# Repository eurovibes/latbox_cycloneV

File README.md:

<!-- SPDX-FileCopyrightText: 2022 Benedikt Spranger <b.spranger@linutronix.de> -->
<!-- SPDX-License-Identifier: CERN-OHL-S-2.0 -->

# latbox_cycloneV - Cyclone V based latencybox

## License rules

latbox_cycloneV is provided under the terms of the CERN-OHL-S license
version 2 as provided in the LICENSES/CERN-OHL-S-2.0 file.

Instead of adding license boilerplates to the individual files,
latbox_cycloneV uses SPDX license identifiers, which are machine parseable
and considered legaly equivalent.

The SPDX license identifier in latbox_cycloneV shall be added at the first
possible line in a file which can contain a comment. This is normally the
first line except for scripts. Scripts require the #!PATH_TO_INTERPRETER tag
in the first line; place the SPDX identifier into the second line.

The SPDX license identifier is added in form of a comment.

## Copyright and License

Copyright Benedikt Spranger 2022.
This source describes Open Hardware and is licensed under the CERNOHL-S v2.
You may redistribute and modify this source and make products using it
under the terms of the CERN-OHL-S v2
(https://ohwr.org/cern ohl s v2.txt ).
This source is distributed WITHOUT ANY EXPRESS OR IMPLIED
WARRANTY, INCLUDING OF MERCHANTABILITY, SATISFACTORY
QUALITY AND FITNESS FOR A PARTICULAR PURPOSE. Please see
the CERN-OHL-S v2 for applicable conditions.
Source location: https://github.com/eurovibes/latbox_cycloneV
As per CERN-OHL-S v2 section 4, should You produce hardware based
on this source, You must where practicable maintain the Source Location
visible on the external case of the latbox_cycloneV or other products you
make using this source.

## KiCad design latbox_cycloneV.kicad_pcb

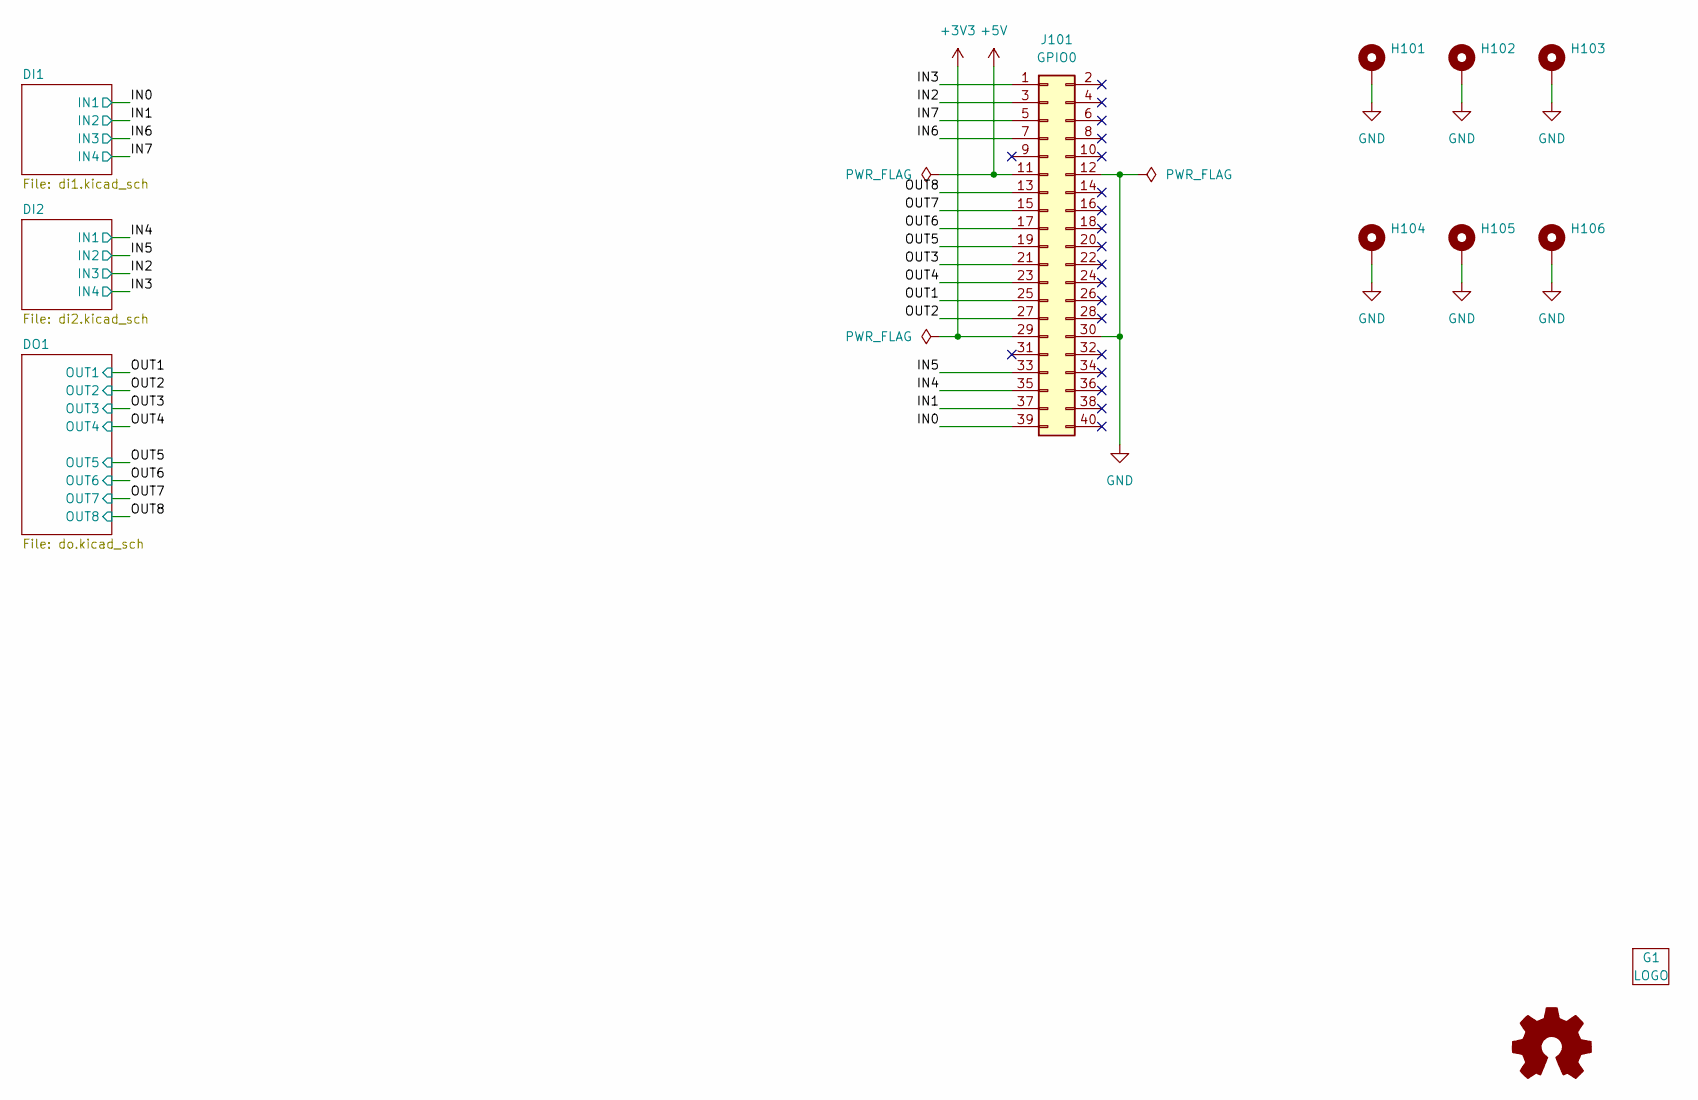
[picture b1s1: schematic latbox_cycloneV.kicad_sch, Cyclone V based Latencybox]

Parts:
G1: LOGO
H101, H102, H103, H104, H105, H106: MountingHole_3.2mm_M3_ISO14580_Pad
J101: GPIO0; PinSocket_2x20_P2.54mm_Vertical

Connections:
+3V3: J101.29
+5V: J101.11; also elsewhere on the board
/IN0: J101.39; also elsewhere on the board
/IN1: J101.37; also elsewhere on the board
/IN2: J101.3; also elsewhere on the board
/IN3: J101.1; also elsewhere on the board
/IN4: J101.35; also elsewhere on the board
/IN5: J101.33; also elsewhere on the board
/IN6: J101.7; also elsewhere on the board
/IN7: J101.5; also elsewhere on the board
/OUT1: J101.25; also elsewhere on the board
/OUT2: J101.27; also elsewhere on the board
/OUT3: J101.21; also elsewhere on the board
/OUT4: J101.23; also elsewhere on the board
/OUT5: J101.19; also elsewhere on the board
/OUT6: J101.17; also elsewhere on the board
/OUT7: J101.15; also elsewhere on the board
/OUT8: J101.13; also elsewhere on the board
GND: H101.1, H102.1, H103.1, H104.1, H105.1, H106.1, J101.12, J101.30; also elsewhere on the board

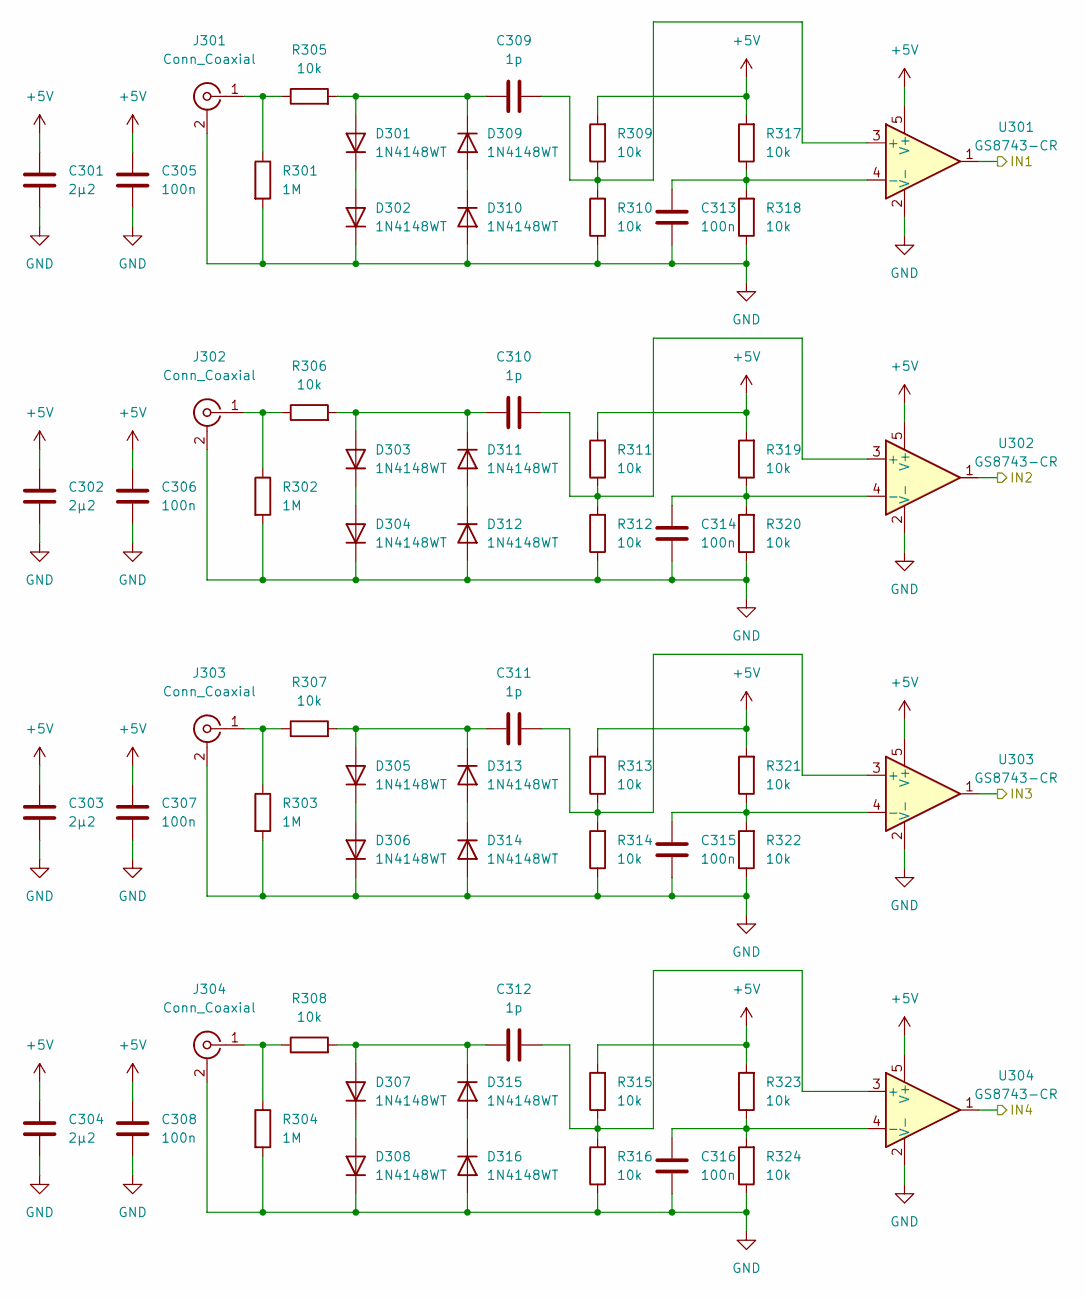
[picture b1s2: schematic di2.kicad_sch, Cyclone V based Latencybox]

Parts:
C301, C302, C303, C304: 2µ2; C_0402_1005Metric; ManuPart# C1005X5R1V225KT000E; LCSC C342966
C305, C306, C307, C308, C313, C314, C315, C316: 100n; C_0402_1005Metric; ManuPart# 0402F104M500NT; LCSC C1581
C309, C310, C311, C312: 1p; C_0402_1005Metric; ManuPart# 0402CG1R0C500NT; LCSC C1550
D301, D302, D303, D304, D305, D306, D307, D308, D309, D310, D311, D312, D313, D314, D315, D316: 1N4148WT; D_SOD-523; ManuPart# 1N4148WT; LCSC C2909971
J301, J302, J303, J304: Conn_Coaxial; BNC_TEConnectivity_1478204_Vertical; ManuPart# 5-1634503-1
R301, R302, R303, R304: 1M; R_0402_1005Metric; ManuPart# RC0402FR-071ML; LCSC C26083
R305, R306, R307, R308, R309, R310, R311, R312, R313, R314, R315, R316, R317, R318, R319, R320, R321, R322, R323, R324: 10k; R_0402_1005Metric; ManuPart# RC0402FR-0710KL; LCSC C138033
U301, U302, U303, U304: GS8743-CR; SOT-353_SC-70-5; ManuPart# GS8743-CR; LCSC C2927685

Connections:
+5V: C301.2, C302.2, C303.2, C304.2, C305.2, C306.2, C307.2, C308.2, R309.2, R311.2, R313.2, R315.2, R317.2, R319.2, R321.2, R323.2, U301.5 (V+), U302.5 (V+), U303.5 (V+), U304.5 (V+); also elsewhere on the board
/IN2: U303.1; also elsewhere on the board
/IN3: U304.1; also elsewhere on the board
/IN4: U301.1; also elsewhere on the board
/IN5: U302.1; also elsewhere on the board
GND: C301.1, C302.1, C303.1, C304.1, C305.1, C306.1, C307.1, C308.1, C313.1, C314.1, C315.1, C316.1, D302.1 (K), D304.1 (K), D306.1 (K), D308.1 (K), D310.2 (A), D312.2 (A), D314.2 (A), D316.2 (A), J301.2 (Ext), J302.2 (Ext), J303.2 (Ext), J304.2 (Ext), R301.2, R302.2, R303.2, R304.2, R310.1, R312.1, R314.1, R316.1, R318.1, R320.1, R322.1, R324.1, U301.2 (V-), U302.2 (V-), U303.2 (V-), U304.2 (V-); also elsewhere on the board
unnamed: C309.1, D301.2 (A), D309.1 (K), R305.2
unnamed: C309.2, R309.1, R310.2, U301.3 (+)
unnamed: C310.1, D303.2 (A), D311.1 (K), R306.2
unnamed: C310.2, R311.1, R312.2, U302.3 (+)
unnamed: C311.1, D305.2 (A), D313.1 (K), R307.2
unnamed: C311.2, R313.1, R314.2, U303.3 (+)
unnamed: C312.1, D307.2 (A), D315.1 (K), R308.2
unnamed: C312.2, R315.1, R316.2, U304.3 (+)
unnamed: C313.2, R317.1, R318.2, U301.4 (-)
unnamed: C314.2, R319.1, R320.2, U302.4 (-)
unnamed: C315.2, R321.1, R322.2, U303.4 (-)
unnamed: C316.2, R323.1, R324.2, U304.4 (-)
unnamed: D301.1 (K), D302.2 (A)
unnamed: D303.1 (K), D304.2 (A)
unnamed: D305.1 (K), D306.2 (A)
unnamed: D307.1 (K), D308.2 (A)
unnamed: D309.2 (A), D310.1 (K)
unnamed: D311.2 (A), D312.1 (K)
unnamed: D313.2 (A), D314.1 (K)
unnamed: D315.2 (A), D316.1 (K)
unnamed: J301.1 (In), R301.1, R305.1
unnamed: J302.1 (In), R302.1, R306.1
unnamed: J303.1 (In), R303.1, R307.1
unnamed: J304.1 (In), R304.1, R308.1

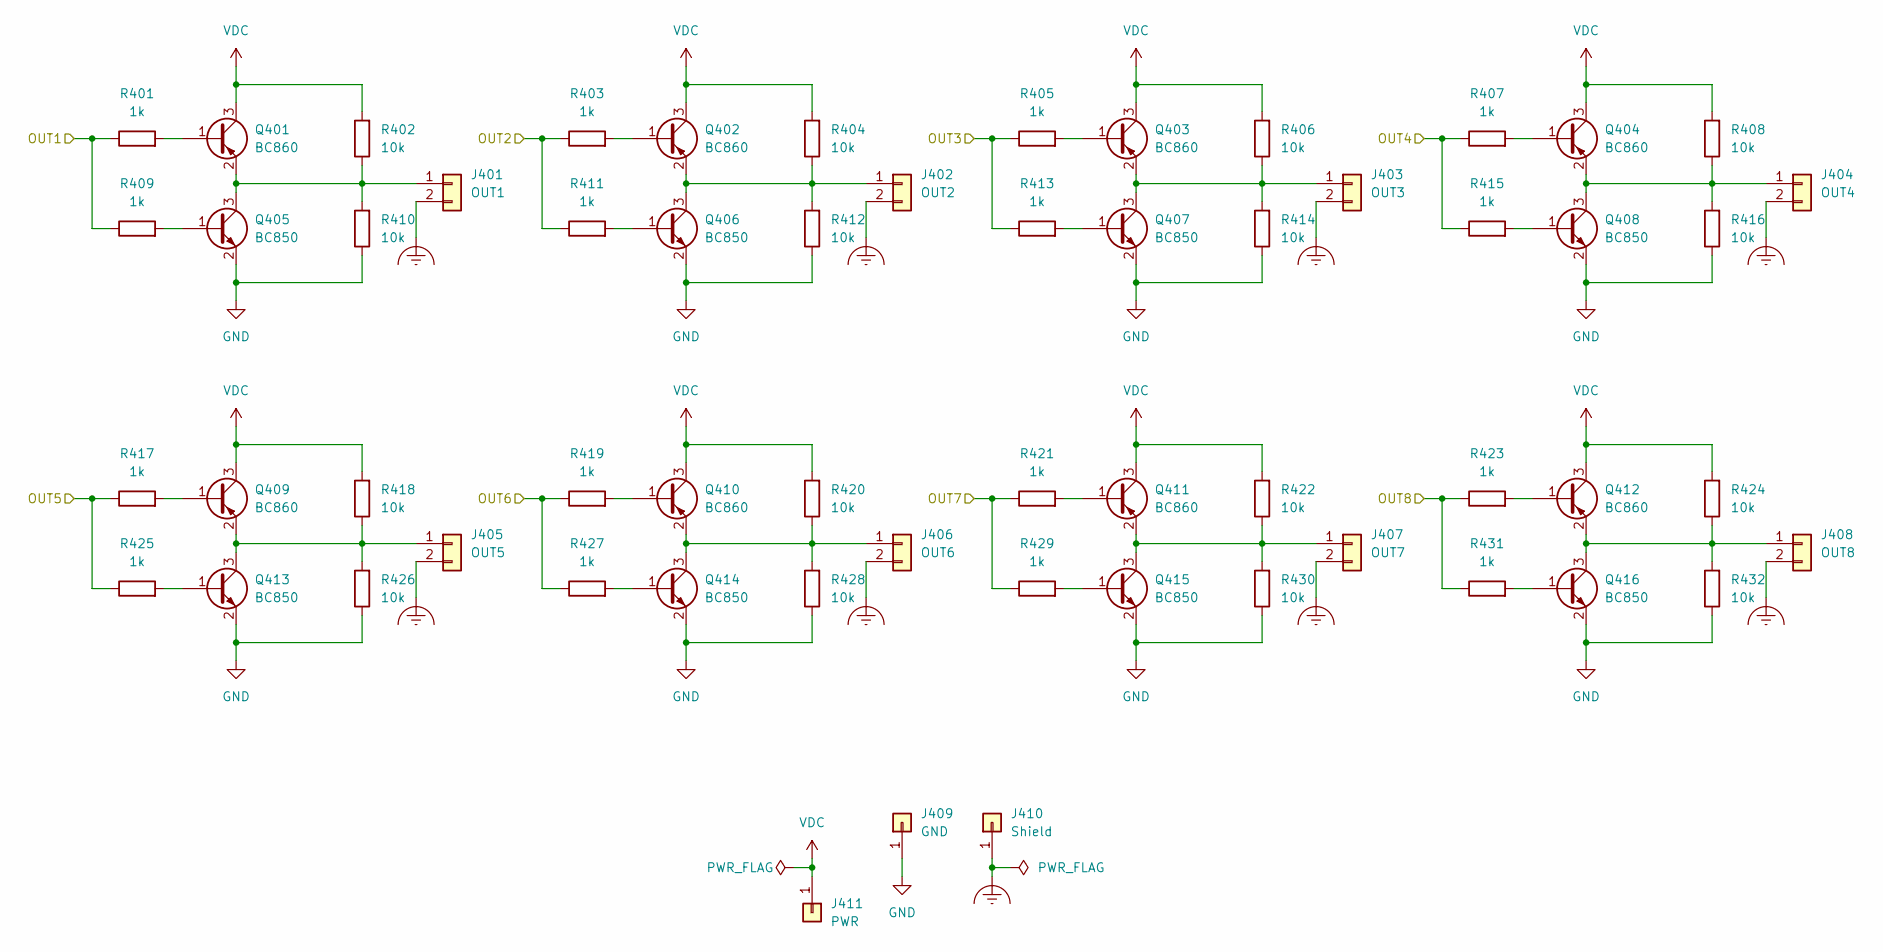
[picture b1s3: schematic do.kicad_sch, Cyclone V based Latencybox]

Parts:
J401: OUT1; SolderWire-2.5sqmm_1x02_P7.2mm_D2.4mm_OD3.6mm
J402: OUT2; SolderWire-2.5sqmm_1x02_P7.2mm_D2.4mm_OD3.6mm
J403: OUT3; SolderWire-2.5sqmm_1x02_P7.2mm_D2.4mm_OD3.6mm
J404: OUT4; SolderWire-2.5sqmm_1x02_P7.2mm_D2.4mm_OD3.6mm
J405: OUT5; SolderWire-2.5sqmm_1x02_P7.2mm_D2.4mm_OD3.6mm
J406: OUT6; SolderWire-2.5sqmm_1x02_P7.2mm_D2.4mm_OD3.6mm
J407: OUT7; SolderWire-2.5sqmm_1x02_P7.2mm_D2.4mm_OD3.6mm
J408: OUT8; SolderWire-2.5sqmm_1x02_P7.2mm_D2.4mm_OD3.6mm
J409: GND; SolderWire-2.5sqmm_1x01_D2.4mm_OD3.6mm
J410: Shield; SolderWire-2.5sqmm_1x01_D2.4mm_OD3.6mm
J411: PWR; SolderWire-2.5sqmm_1x01_D2.4mm_OD3.6mm
Q401, Q402, Q403, Q404, Q409, Q410, Q411, Q412: BC860; SOT-23; ManuPart# BC860B,215; LCSC C454954
Q405, Q406, Q407, Q408, Q413, Q414, Q415, Q416: BC850; SOT-23; ManuPart# BC850B,215; LCSC C503377
R401, R403, R405, R407, R409, R411, R413, R415, R417, R419, R421, R423, R425, R427, R429, R431: 1k; R_0402_1005Metric; ManuPart# RC0402FR-071KL; LCSC C106235
R402, R404, R406, R408, R410, R412, R414, R416, R418, R420, R422, R424, R426, R428, R430, R432: 10k; R_0402_1005Metric; ManuPart# RC0402FR-0710KL; LCSC C138033

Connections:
/OUT1: R401.1, R409.1; also elsewhere on the board
/OUT2: R403.1, R411.1; also elsewhere on the board
/OUT3: R405.1, R413.1; also elsewhere on the board
/OUT4: R407.1, R415.1; also elsewhere on the board
/OUT5: R417.1, R425.1; also elsewhere on the board
/OUT6: R419.1, R427.1; also elsewhere on the board
/OUT7: R421.1, R429.1; also elsewhere on the board
/OUT8: R423.1, R431.1; also elsewhere on the board
Earth_Clean: J401.2, J402.2, J403.2, J404.2, J405.2, J406.2, J407.2, J408.2, J410.1
GND: J409.1, Q405.2 (E), Q406.2 (E), Q407.2 (E), Q408.2 (E), Q413.2 (E), Q414.2 (E), Q415.2 (E), Q416.2 (E), R410.1, R412.1, R414.1, R416.1, R426.1, R428.1, R430.1, R432.1; also elsewhere on the board
unnamed: J401.1, Q401.2 (E), Q405.3 (C), R402.1, R410.2
unnamed: J402.1, Q402.2 (E), Q406.3 (C), R404.1, R412.2
unnamed: J403.1, Q403.2 (E), Q407.3 (C), R406.1, R414.2
unnamed: J404.1, Q404.2 (E), Q408.3 (C), R408.1, R416.2
unnamed: J405.1, Q409.2 (E), Q413.3 (C), R418.1, R426.2
unnamed: J406.1, Q410.2 (E), Q414.3 (C), R420.1, R428.2
unnamed: J407.1, Q411.2 (E), Q415.3 (C), R422.1, R430.2
unnamed: J408.1, Q412.2 (E), Q416.3 (C), R424.1, R432.2
unnamed: Q401.1 (B), R401.2
unnamed: Q402.1 (B), R403.2
unnamed: Q403.1 (B), R405.2
unnamed: Q404.1 (B), R407.2
unnamed: Q405.1 (B), R409.2
unnamed: Q406.1 (B), R411.2
unnamed: Q407.1 (B), R413.2
unnamed: Q408.1 (B), R415.2
unnamed: Q409.1 (B), R417.2
unnamed: Q410.1 (B), R419.2
unnamed: Q411.1 (B), R421.2
unnamed: Q412.1 (B), R423.2
unnamed: Q413.1 (B), R425.2
unnamed: Q414.1 (B), R427.2
unnamed: Q415.1 (B), R429.2
unnamed: Q416.1 (B), R431.2
VDC: J411.1, Q401.3 (C), Q402.3 (C), Q403.3 (C), Q404.3 (C), Q409.3 (C), Q410.3 (C), Q411.3 (C), Q412.3 (C), R402.2, R404.2, R406.2, R408.2, R418.2, R420.2, R422.2, R424.2

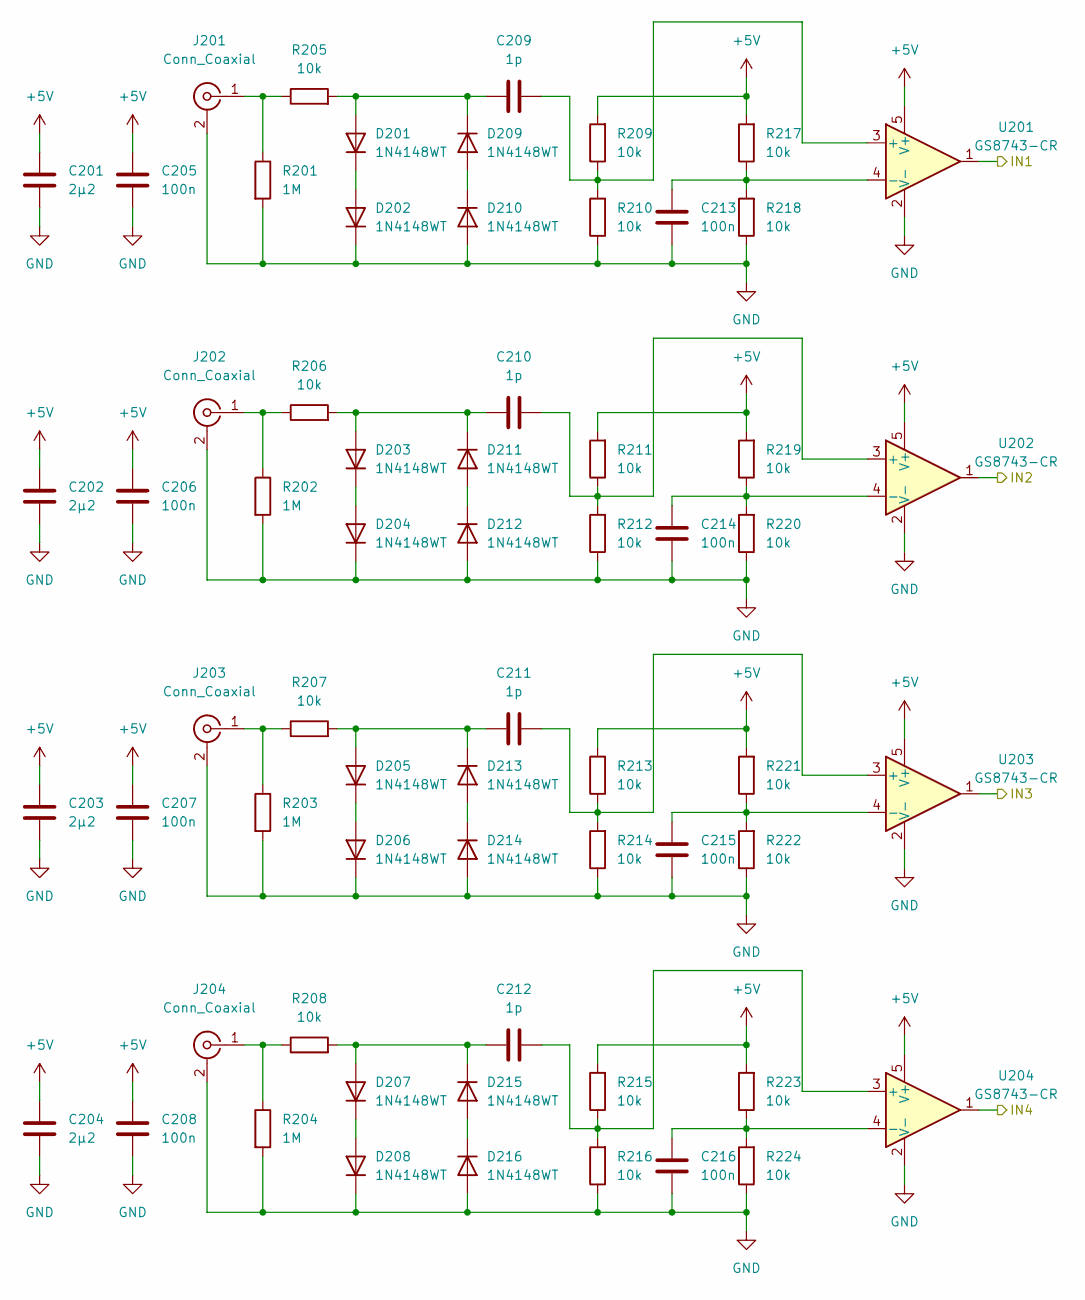
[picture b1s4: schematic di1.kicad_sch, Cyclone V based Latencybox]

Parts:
C201, C202, C203, C204: 2µ2; C_0402_1005Metric; ManuPart# C1005X5R1V225KT000E; LCSC C342966
C205, C206, C207, C208, C213, C214, C215, C216: 100n; C_0402_1005Metric; ManuPart# 0402F104M500NT; LCSC C1581
C209, C210, C211, C212: 1p; C_0402_1005Metric; ManuPart# 0402CG1R0C500NT; LCSC C1550
D201, D202, D203, D204, D205, D206, D207, D208, D209, D210, D211, D212, D213, D214, D215, D216: 1N4148WT; D_SOD-523; ManuPart# 1N4148WT; LCSC C2909971
J201, J202, J203, J204: Conn_Coaxial; BNC_TEConnectivity_1478204_Vertical; ManuPart# 5-1634503-1
R201, R202, R203, R204: 1M; R_0402_1005Metric; ManuPart# RC0402FR-071ML; LCSC C26083
R205, R206, R207, R208, R209, R210, R211, R212, R213, R214, R215, R216, R217, R218, R219, R220, R221, R222, R223, R224: 10k; R_0402_1005Metric; ManuPart# RC0402FR-0710KL; LCSC C138033
U201, U202, U203, U204: GS8743-CR; SOT-353_SC-70-5; ManuPart# GS8743-CR; LCSC C2927685

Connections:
+5V: C201.2, C202.2, C203.2, C204.2, C205.2, C206.2, C207.2, C208.2, R209.2, R211.2, R213.2, R215.2, R217.2, R219.2, R221.2, R223.2, U201.5 (V+), U202.5 (V+), U203.5 (V+), U204.5 (V+); also elsewhere on the board
/IN0: U201.1; also elsewhere on the board
/IN1: U202.1; also elsewhere on the board
/IN6: U203.1; also elsewhere on the board
/IN7: U204.1; also elsewhere on the board
GND: C201.1, C202.1, C203.1, C204.1, C205.1, C206.1, C207.1, C208.1, C213.1, C214.1, C215.1, C216.1, D202.1 (K), D204.1 (K), D206.1 (K), D208.1 (K), D210.2 (A), D212.2 (A), D214.2 (A), D216.2 (A), J201.2 (Ext), J202.2 (Ext), J203.2 (Ext), J204.2 (Ext), R201.2, R202.2, R203.2, R204.2, R210.1, R212.1, R214.1, R216.1, R218.1, R220.1, R222.1, R224.1, U201.2 (V-), U202.2 (V-), U203.2 (V-), U204.2 (V-); also elsewhere on the board
unnamed: C209.1, D201.2 (A), D209.1 (K), R205.2
unnamed: C209.2, R209.1, R210.2, U201.3 (+)
unnamed: C210.1, D203.2 (A), D211.1 (K), R206.2
unnamed: C210.2, R211.1, R212.2, U202.3 (+)
unnamed: C211.1, D205.2 (A), D213.1 (K), R207.2
unnamed: C211.2, R213.1, R214.2, U203.3 (+)
unnamed: C212.1, D207.2 (A), D215.1 (K), R208.2
unnamed: C212.2, R215.1, R216.2, U204.3 (+)
unnamed: C213.2, R217.1, R218.2, U201.4 (-)
unnamed: C214.2, R219.1, R220.2, U202.4 (-)
unnamed: C215.2, R221.1, R222.2, U203.4 (-)
unnamed: C216.2, R223.1, R224.2, U204.4 (-)
unnamed: D201.1 (K), D202.2 (A)
unnamed: D203.1 (K), D204.2 (A)
unnamed: D205.1 (K), D206.2 (A)
unnamed: D207.1 (K), D208.2 (A)
unnamed: D209.2 (A), D210.1 (K)
unnamed: D211.2 (A), D212.1 (K)
unnamed: D213.2 (A), D214.1 (K)
unnamed: D215.2 (A), D216.1 (K)
unnamed: J201.1 (In), R201.1, R205.1
unnamed: J202.1 (In), R202.1, R206.1
unnamed: J203.1 (In), R203.1, R207.1
unnamed: J204.1 (In), R204.1, R208.1

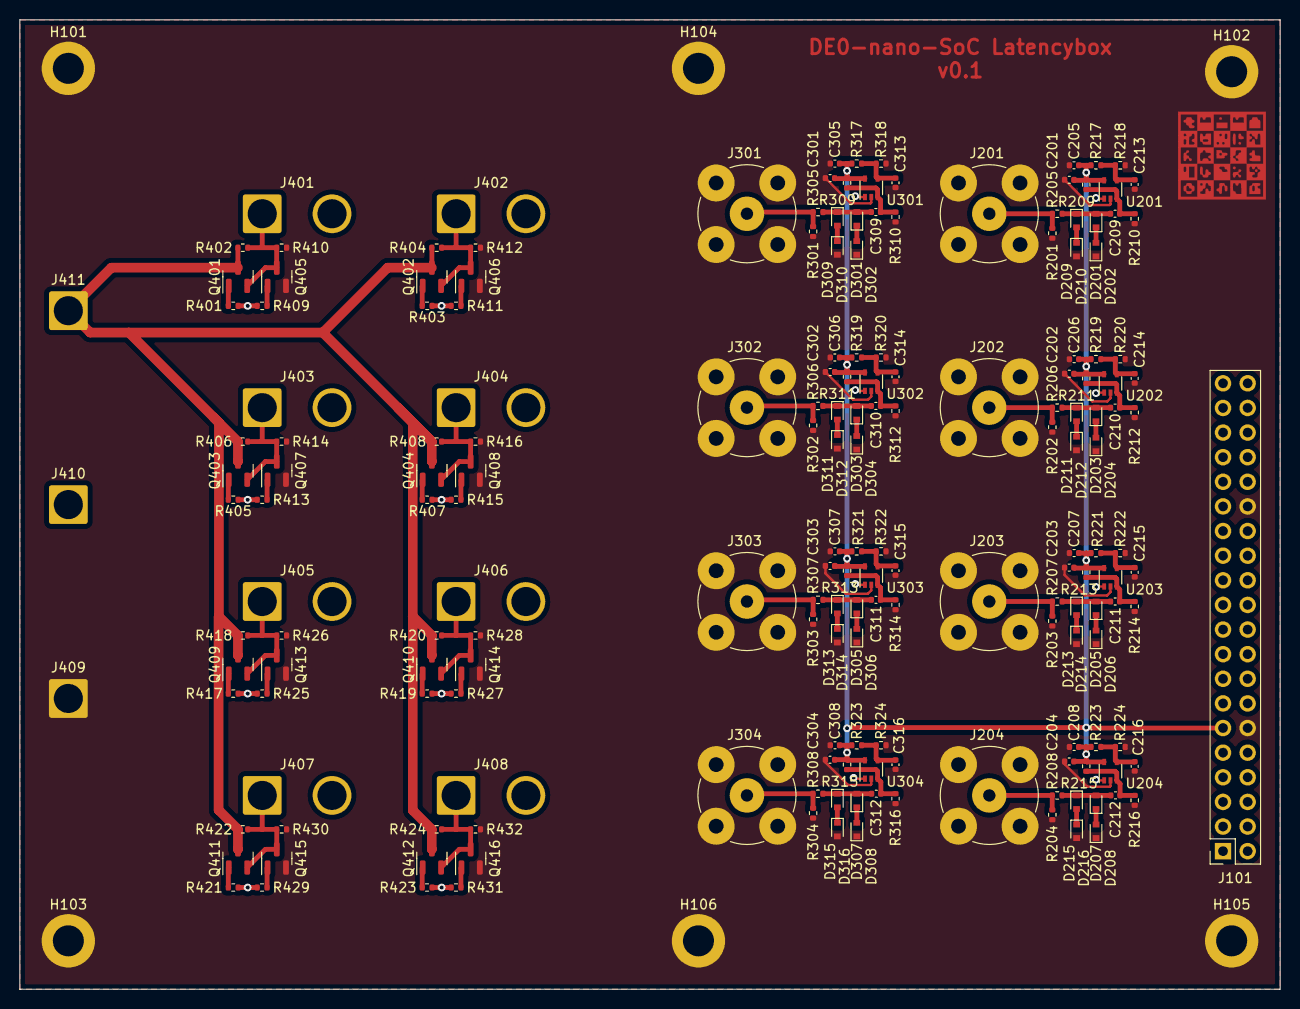
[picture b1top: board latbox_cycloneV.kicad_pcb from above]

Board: 4 copper layers, 130.0 x 100.0 mm, 195 parts (0 on the bottom side), 92 nets.

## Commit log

2022-01-18 Use KiBot master
2022-01-18 Initial
2022-01-19 Add Eurovibes Logo
2022-01-19 Add markings
2022-01-19 Initial gh page
    Add gh pages for project documentation.
2022-01-19 Deploying to gh-pages from @ eurovibes/latbox_cycloneV@897ea0a0338b7e9b02e2d2353bd8f7d8138adc8c 🚀

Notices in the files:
di1.kicad_sch:
This work is licensed under the CERN-OHL-S v2
